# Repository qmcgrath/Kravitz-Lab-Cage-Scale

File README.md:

# Kravitz-Lab-Cage-Scale
Quinlan McGrath, Robbie Schaefer, Lex Kravitz, Gunwoo Lee

  The use of food and water restriction, drugs, surgery, and disease models in live mouse studies require continuous monitoring of body weight to surveill mouse health and determine experiment endpoints. Resolution of weight fluctuation over time can offer researchers a more complete picture of mouse health. Traditional manual weighing induces stress in mice and disrupts circadian rhythms.Existing commercial and open source autonomous mouse weight systems are available. However, commercial systems are not cost effective, cannot be used in colonial housing cages, or required rFID tags. 
 
Accurate, non-invasive recording of mouse weight allows for increased volume of body weight data while decreasing animal stress and human interaction. The developed scale can be constructed for $150 and operates for ~3.5 days on one charge. It has a small footprint of 7.6x8.6x8 cm and can be used in singley housed mice in traditional vivarium cages without modification. An Hx711 and proximity sensor work in tandem to determine mouse weight readings. The scale is operates on open source arduino code and data is anlysised with provided python code. 
  
  It was demonstrated that the scale can acheived and estimation of mouse weight with an average of 1.55% error with 50% hourly resolution (22 instances). Hourly resolution can be increased to 100% at the expense of an increased average error of 1.66% (33 instances). Accuracy was determined via comparision of maunaul weighing and reported weights for the same hour. Twenty two instances were used. It was demonstrated that this scale has potential appications in circadian rhythm monitoring, energy expendature evaluation, and group housed mice.  
  
 Assemebly, hardware and software overviews, quick start instructions, and code documentation are available in the wiki. The Jupyter notebooks used for data anlysis are provided. 

A graphical overview of embedded logic is shown below. 

## Results
Three scales (labeled A, B, C) were constructed and included in testing procedures. Individually house mice were monitored continuously for an average of 5 days. Manual weights were recorded at 33 instances.  

Code and data used are available above. The manual recorded weights are available in 'example data'.

Figure 1: Visualization of the basic scale operations. 

Figure 2: Reported hourly weight (g) vs Time (hour)

The methodology for calcuting the hourly weight from the scale data was simple. First, any report cgrams < 15 g were dropped, as it can be assumed these were recorded when the mouse was only partially on the scale. Next, the data was binned into hours and the median was found. Median weights were found to be more accurate than mode data. For further evaluation, a 'minimum number of cgram recordings per hour' was selected in which a reported weight could be deemed reliable or well informed. An array of minimum number counts, the resultant accuracy and resolution, and instances count (# of hours for which there was a manual weight available) are reported in Table 1. As shown, the average error is a minimum at a 150 instance thresehold. However, 100 data points was choosen as the optimal value as it has a higher resolution (nearly 50%) for minimum accuracy gain. Thus, it was determined that the scale can determine mouse weight with an accuracy of 1.55% with 50% resolution.

Figure 3: Weight error percent distribution. 

Table 1 was recreated for data in which hourly median weight was interpolated across hours with insufficient cgrams were reported. This increased resolution to 100%, will only minorly increasing overall error to 1.66%. 

However, it can be seen in the color coded histogram that not all scales performed equally. In fact, Table 3 demonstrates the distribution of error across the scales - with scale A outperforming the other two substaintially.

### Next Steps 
- More user friendly 3d design 
- improved calibration code

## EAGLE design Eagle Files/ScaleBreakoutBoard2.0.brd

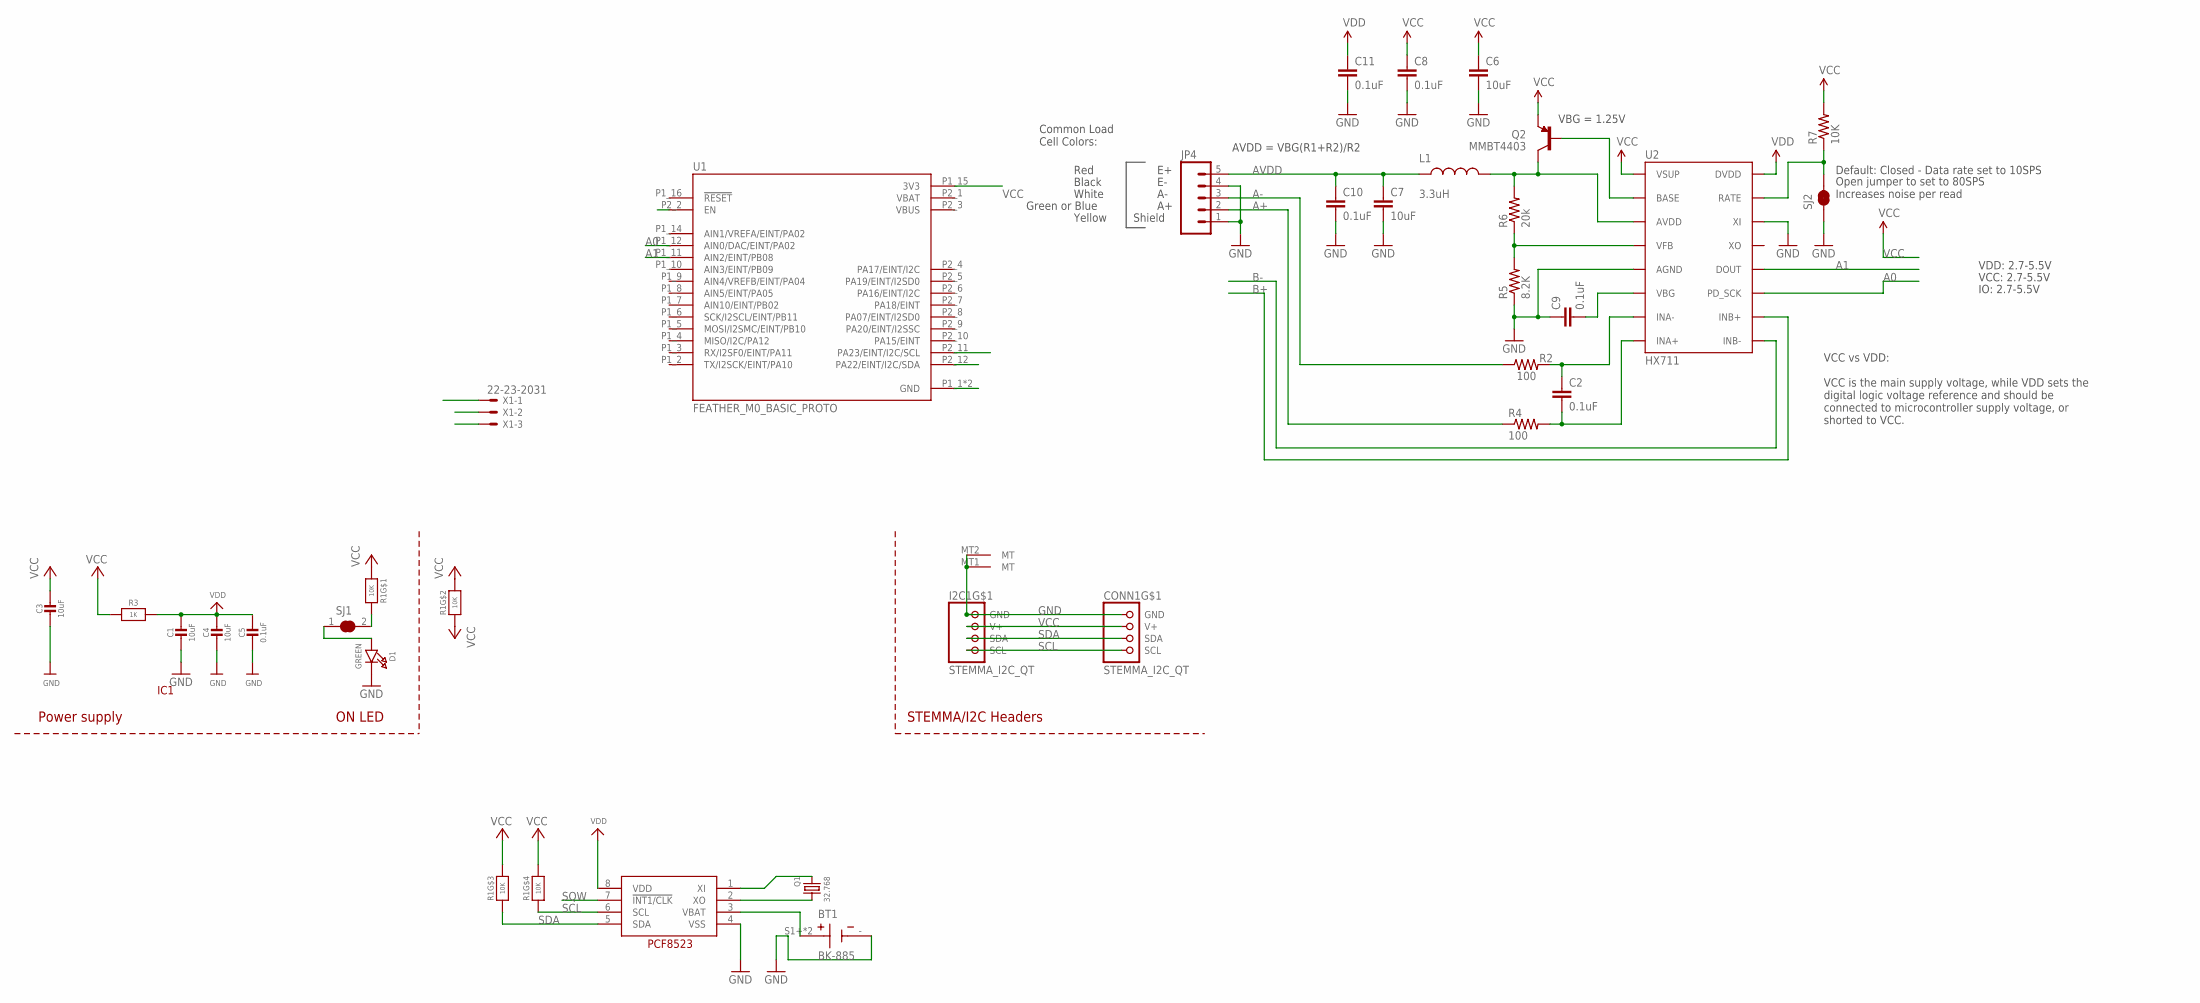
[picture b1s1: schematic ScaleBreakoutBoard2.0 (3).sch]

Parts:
BT1: BK-885; BAT_BK-885
C1, C3, C4: 10uF; 0805-NO
C2, C8, C9, C10, C11: 0.1uF; 0603-CAP
C5: 0.1uF; 0603-NO
C6, C7: 10uF; 1210
CONN1: STEMMA_I2C_QT; JST_SH4
D1: GREEN; CHIPLED_0603_NOOUTLINE
I2C1: STEMMA_I2C_QT; JST_SH4
IC1: RTC_PCF8523T; SOIC8_150MIL
JP4: M05PTH; 1X05
L1: 3.3uH; 0805
Q1: 32.768; XTAL3215
Q2: MMBT4403; SOT23-3
R1: 10K; RESPACK_4X0603
R2, R4: 100; 0603-RES
R3: 1K; 0603-NO
R5: 8.2K; 0603-RES
R6: 20k; 0603-RES
R7: 10K; 0603-RES
SJ1: SOLDERJUMPER_CLOSED; SOLDERJUMPER_CLOSEDWIRE
SJ2: JUMPER-PAD-2-NC_BY_TRACE; PAD-JUMPER-2-NC_BY_TRACE_YES_SILK
U1: FEATHER_M0_BASIC_PROTO; MODULE_FEATHER_M0_BASIC_PROTO
U2: HX711; SO16
X1: 22-23-2031

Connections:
A0: U1.P1_12 (AIN0/DAC/EINT/PA02), U2.11 (PD_SCK)
A1: U1.P1_11 (AIN2/EINT/PB08), U2.12 (DOUT)
A+: JP4.2, R4.1
A-: JP4.3, R2.1
AVDD: C7.1, C10.1, JP4.5, L1.1
B+: U2.10 (INB+)
B-: U2.9 (INB-)
EN: U1.P2_2 (EN), X1.3
GND: BT1.-, C1.2, C3.2, C4.2, C5.2, C6.2, C7.2, C8.2, C9.1, C10.2, C11.2, CONN1.1 (GND), D1.C, I2C1.1 (GND), I2C1.MT1 (MT), I2C1.MT2 (MT), IC1.4 (VSS), JP4.1, JP4.4, R5.1, SJ2.1, U1.P1_1 (GND), U1.P1_13 (GND), U2.5 (AGND), U2.14 (XI), X1.1, X1.2
unnamed: R1.8 (2), SJ1.2
unnamed: Q2.1 (B), U2.2 (BASE)
unnamed: R7.1, SJ2.2, U2.15 (RATE)
unnamed: D1.A, SJ1.1
unnamed: L1.2, Q2.3 (C), R6.2, U2.3 (AVDD)
unnamed: R5.2, R6.1, U2.4 (VFB)
unnamed: C9.2, U2.6 (VBG)
unnamed: C2.1, R2.2, U2.7 (INA-)
unnamed: C2.2, R4.2, U2.8 (INA+)
unnamed: IC1.1 (XI), Q1.P$1 (1)
unnamed: IC1.2 (XO), Q1.P$2 (2)
SCL: CONN1.4 (SCL), I2C1.4 (SCL), IC1.6 (SCL), R1.4 (1), U1.P2_11 (PA23/EINT/I2C/SCL)
SDA: CONN1.3 (SDA), I2C1.3 (SDA), IC1.5 (SDA), R1.3 (1), U1.P2_12 (PA22/EINT/I2C/SDA)
SQW: IC1.7 (!INT1/CLK)
VBAT: U1.P2_1 (VBAT)
VBAT1: BT1.S1+ (+), BT1.S2+ (+), IC1.3 (VBAT)
VBUS: U1.P2_3 (VBUS)
VCC: C3.1, C6.1, C8.1, CONN1.2 (V+), I2C1.2 (V+), Q2.2 (E), R1.1, R1.2 (1), R1.5 (2), R1.6 (2), R1.7 (2), R3.1, R7.2, U1.P1_15 (3V3), U2.1 (VSUP)
VDD: C1.1, C4.1, C5.1, C11.1, IC1.8 (VDD), R3.2, U2.16 (DVDD)

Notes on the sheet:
STEMMA/I2C Headers
ON LED
Power supply
VCC: 2.7-5.5V
VBG = 1.25V
AVDD = VBG(R1+R2)/R2
Default: Closed - Data rate set to 10SPS
Open jumper to set to 80SPS Increases noise per read
Red
Black
White
Green or Blue
Common Load Cell Colors:
IO: 2.7-5.5V
Shield
Yellow
VDD: 2.7-5.5V
VCC vs VDD: VCC is the main supply voltage, while VDD sets the digital logic voltage reference and should be connected to microcontroller supply voltage, or shorted to VCC.

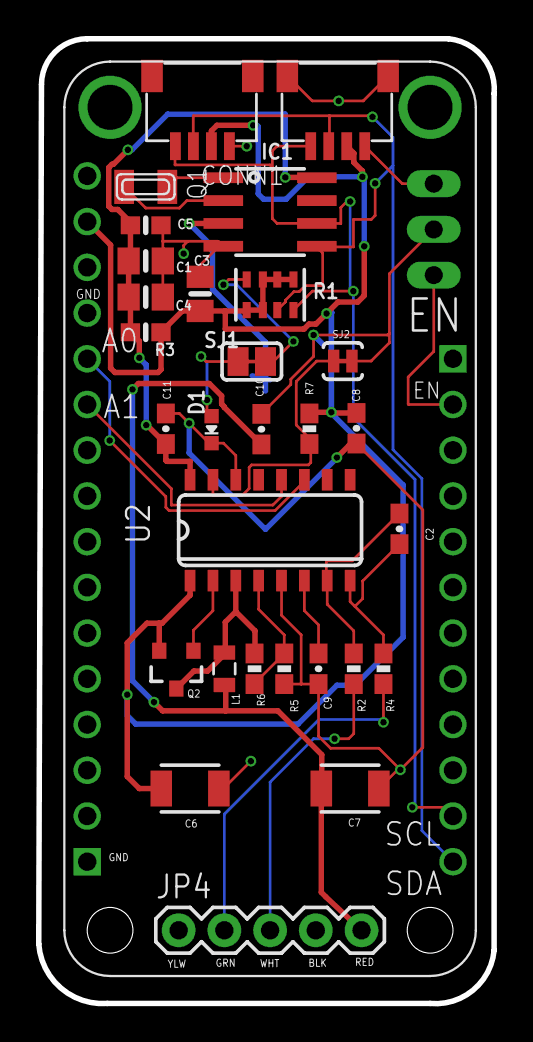
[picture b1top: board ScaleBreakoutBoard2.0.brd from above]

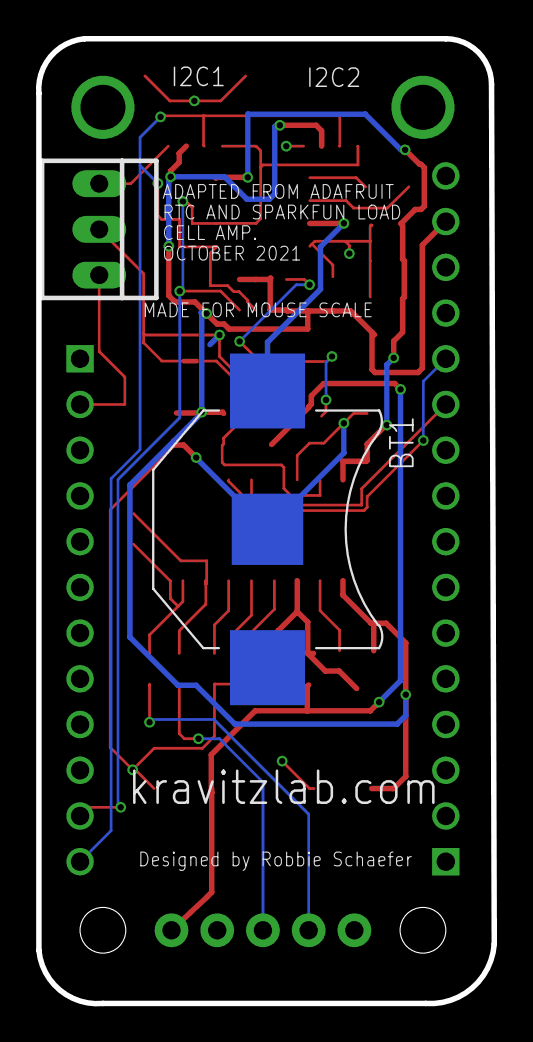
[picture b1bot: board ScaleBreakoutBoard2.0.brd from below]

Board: 2 copper layers, 25.3 x 53.6 mm, 32 parts (2 on the bottom side), 23 nets.

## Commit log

2021-12-03 Add files via upload
    txt files from mouse runs
2021-12-03 Create Data
2022-04-19 Create stlfiles
2022-04-19 Create df
2022-04-19 Create ScaleSchematic
2022-04-19 Create ex
2022-05-09 Create images
2022-05-09 Create buildImages

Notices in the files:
parts and their libraries:
microbuilder: This work is placed in the public domain, and may be freely used for commercial and non-commercial work with the following conditions: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
SparkFun-Aesthetics: Licensing: CC v3.0 Share-Alike You are welcome to use this library for commercial purposes.
